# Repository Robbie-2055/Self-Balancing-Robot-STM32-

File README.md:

# STM32 Self-Balancing Robot

A two-wheeled self-balancing inverted pendulum robot built using an **STM32** microcontroller. The robot utilizes an **MPU6050** Inertial Measurement Unit (IMU) to sense its orientation, processes this data through a PID loop, and drives two **DC shaft motors** via an **L298N** motor driver to maintain perfect equilibrium.

This project is split into two distinct execution phases: prototyping with off-the-shelf modules and migrating to a custom-designed Printed Circuit Board (PCB).

---

## 📌 Project Roadmap

- [x] **Phase 1: Breadboard Prototype** 
  - Wire STM32, MPU6050, and L298N on a chassis.
  - Implement basic I2C communication and PWM motor control.
- [ ] **Phase 2: Firmware Optimization**
  - Tune the PID parameters ($K_p$, $K_i$, $K_d$).
- [ ] **Phase 3: Custom PCB Layout**
  - Design a compact, integrated schematic in KiCad

---

## 🛠️ Hardware Architecture

### Phase 1: Prototype Components
* **Microcontroller:** STM32 (e.g., STM32F103C8T6 "Blue Pill") — Handles high-speed sensor parsing, PID calculation, and PWM generation.
* **IMU Sensor:** MPU6050 — Configured via I2C to read accelerometer and gyroscope raw data.
* **Motor Driver:** L298N Dual H-Bridge — Regulates power and direction to the motors based on logic signals from the STM32.
* **Actuators:** 2x DC Gear Shaft Motors (equipped with quadrature encoders for speed feedback).
* **Power Supply:** 3S LiPo battery (11.1V) to power the motors, stepped down via buck converter to 5V/3.3V for logic.

### Phase 2: Custom Board Upgrades
To reduce wiring complexity, eliminate inductive noise, and minimize the physical footprint:
* **Integrated MCU:** STM32 chip placed directly on-board with dedicated decoupling capacitors and an external crystal oscillator.
* **On-board Sensors:** Hardwired MPU6050 footprint to prevent I2C signal degradation over jumper wires.
* **Motor Driver:** The L298N Motor driver together with all support components placed directly on the custom board

---

## Current developments

https://github.com/user-attachments/assets/f44257d5-607a-4bce-967d-3fb6638ffd92

https://github.com/user-attachments/assets/f6ba3c8e-9986-4cd3-9cd2-4a73ed5fd0c9

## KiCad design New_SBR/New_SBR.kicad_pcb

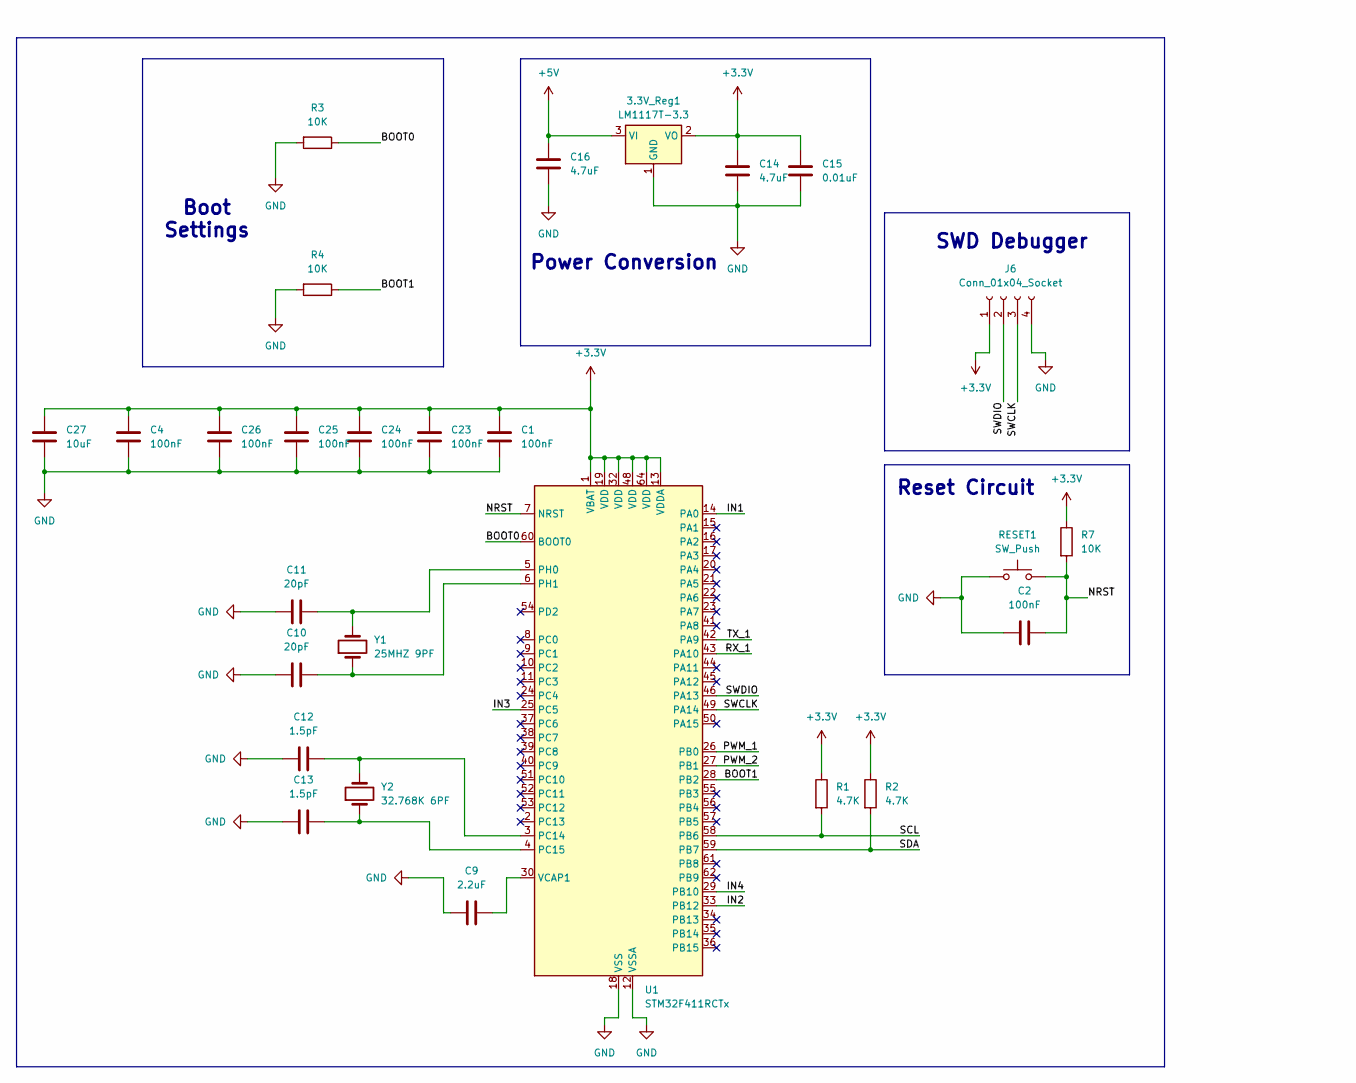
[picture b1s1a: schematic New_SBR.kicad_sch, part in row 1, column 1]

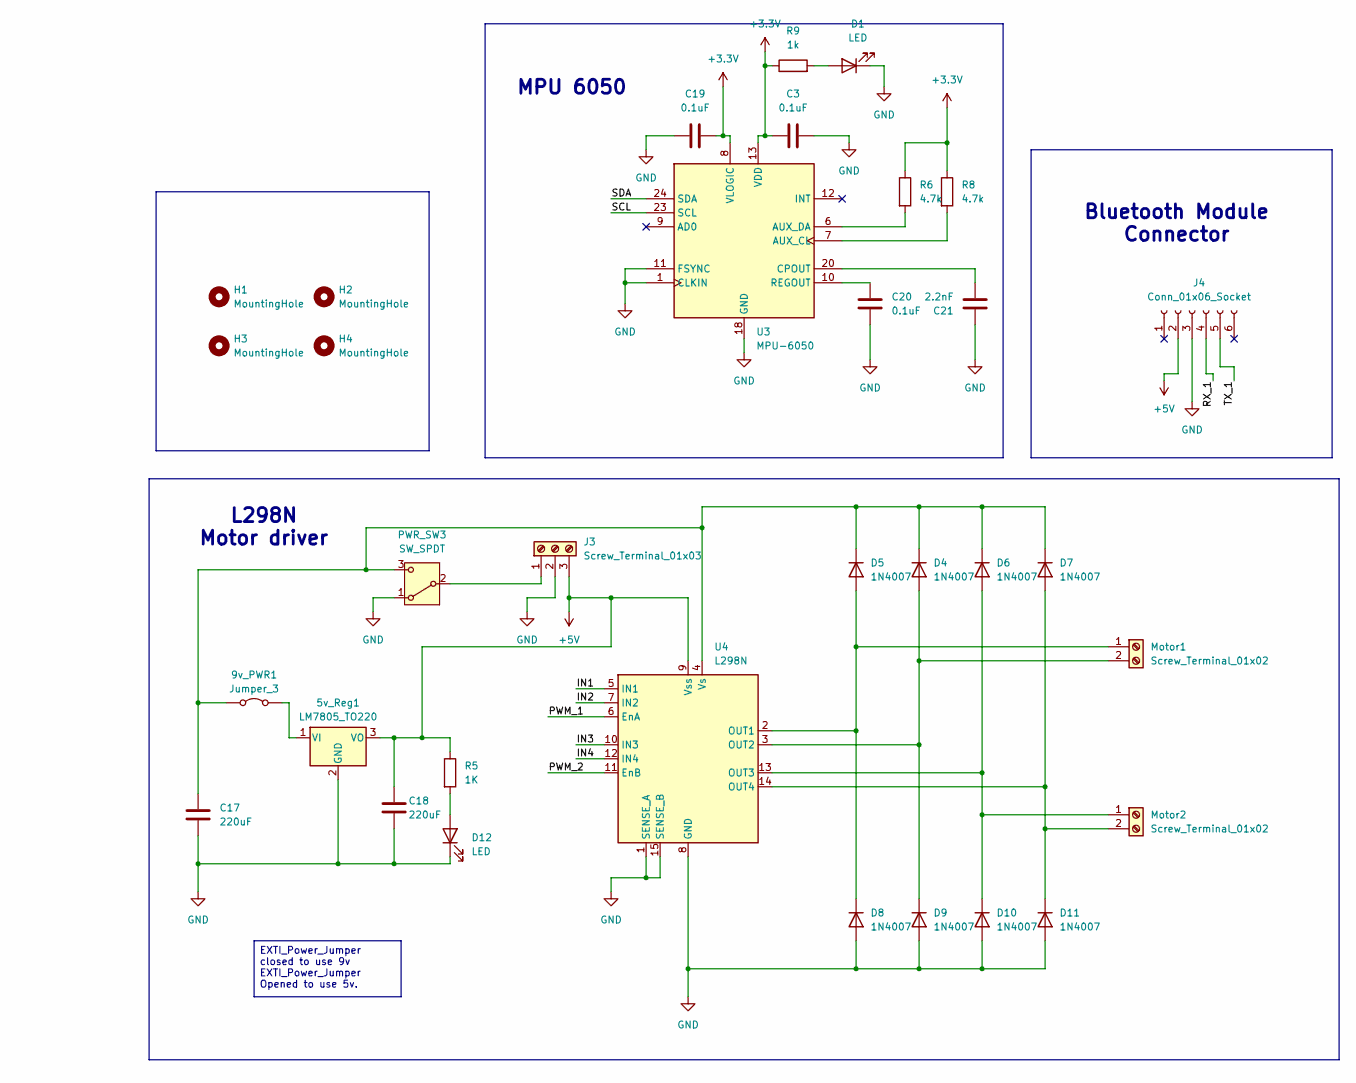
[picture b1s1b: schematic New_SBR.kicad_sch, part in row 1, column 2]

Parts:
3.3V_Reg1: LM1117T-3.3; TO-220-3_Vertical
5v_Reg1: LM7805_TO220; TO-220-3_Vertical
9v_PWR1: Jumper_3; PinHeader_1x02_P2.54mm_Vertical
C1, C2, C4, C23, C24, C25, C26: 100nF; C_0603_1608Metric
C3, C19, C20: 0.1uF; C_0402_1005Metric
C9: 2.2uF; C_0603_1608Metric
C10, C11: 20pF; C_0603_1608Metric
C12, C13: 1.5pF; C_0603_1608Metric
C14, C16: 4.7uF; C_0603_1608Metric
C15: 0.01uF; C_0603_1608Metric
C17, C18: 220uF; C_0603_1608Metric
C21: 2.2nF; C_0402_1005Metric
C27: 10uF; C_0603_1608Metric
D1: LED; LED_0402_1005Metric
D4, D5, D6, D7, D8, D9, D10, D11: 1N4007; D_SMA
D12: LED; LED_0603_1608Metric
H1, H2, H3, H4: MountingHole; MountingHole_2.2mm_M2
J3: Screw_Terminal_01x03; TerminalBlock_Phoenix_MKDS-1,5-3-5.08_1x03_P5.08mm_Horizont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
J4: Conn_01x06_Socket; PinSocket_1x06_P2.54mm_Vertical
J6: Conn_01x04_Socket; PinSocket_1x04_P2.54mm_Vertical
Motor1, Motor2: Screw_Terminal_01x02; TerminalBlock_Phoenix_MKDS-1,5-2-5.08_1x02_P5.08mm_Horizont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
PWR_SW3: SW_SPDT; SW_Slide_SPDT_Straight_CK_OS102011MS2Q
R1, R2: 4.7K; R_0402_1005Metric
R3, R4, R7: 10K; R_0603_1608Metric
R5: 1K; R_0603_1608Metric
R6, R8: 4.7k; R_0402_1005Metric
R9: 1k; R_0402_1005Metric
RESET1: SW_Push; SW_SPST_TL3305A
U1: STM32F411RCTx; LQFP-64_10x10mm_P0.5mm
U3: MPU-6050; InvenSense_QFN-24_4x4mm_P0.5mm_NoMask
U4: L298N; TO-220-15_P2.54x5.08mm_StaggerOdd_Lead4.58mm_Vertical
Y1: 25MHZ 9PF; Crystal_HC49-U_Vertical
Y2: 32.768K 6PF; Crystal_C38-LF_D3.0mm_L8.0mm_Vertical

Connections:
+3.3V: 3.3V_Reg1.2 (VO), C1.2, C3.1, C4.2, C14.2, C15.2, C19.2, C23.2, C24.2, C25.2, C26.2, C27.2, J6.1, R1.1, R2.1, R6.1, R7.1, R8.1, R9.1, U1.1 (VBAT), U1.13 (VDDA), U1.19 (VDD), U1.32 (VDD), U1.48 (VDD), U1.64 (VDD), U3.8 (VLOGIC), U3.13 (VDD)
+5V: 3.3V_Reg1.3 (VI), 5v_Reg1.3 (VO), C16.2, C18.2, J3.3, J4.2, R5.1, U4.9 (Vss)
/BOOT0: R3.1, U1.60 (BOOT0)
/BOOT1: R4.1, U1.28 (PB2)
/IN1: U1.14 (PA0), U4.5 (IN1)
/IN2: U1.33 (PB12), U4.7 (IN2)
/IN3: U1.25 (PC5), U4.10 (IN3)
/IN4: U1.29 (PB10), U4.12 (IN4)
/NRST: C2.1, R7.2, RESET1.2, U1.7 (NRST)
/PWM_1: U1.26 (PB0), U4.6 (EnA)
/PWM_2: U1.27 (PB1), U4.11 (EnB)
/RX_1: J4.4, U1.43 (PA10)
/SCL: R1.2, U1.58 (PB6), U3.23 (SCL)
/SDA: R2.2, U1.59 (PB7), U3.24 (SDA)
/SWCLK: J6.3, U1.49 (PA14)
/SWDIO: J6.2, U1.46 (PA13)
/TX_1: J4.5, U1.42 (PA9)
GND: 3.3V_Reg1.1 (GND), 5v_Reg1.2 (GND), C1.1, C2.2, C3.2, C4.1, C9.1, C10.1, C11.1, C12.1, C13.1, C14.1, C15.1, C16.1, C17.1, C18.1, C19.1, C20.1, C21.2, C23.1, C24.1, C25.1, C26.1, C27.1, D1.1 (K), D8.2 (A), D9.2 (A), D10.2 (A), D11.2 (A), D12.1 (K), J3.2, J4.3, J6.4, PWR_SW3.1 (A), R3.2, R4.2, RESET1.1, U1.12 (VSSA), U1.18 (VSS), U1.31 (VSS), U1.47 (VSS), U1.63 (VSS), U3.1 (CLKIN), U3.11 (FSYNC), U3.18 (GND), U4.1 (SENSE_A), U4.8 (GND), U4.15 (SENSE_B)
unnamed: 5v_Reg1.1 (VI), 9v_PWR1.2 (B)
unnamed: 9v_PWR1.1 (A), C17.2, D4.1 (K), D5.1 (K), D6.1 (K), D7.1 (K), PWR_SW3.3 (C), U4.4 (Vs)
unnamed: D1.2 (A), R9.2
unnamed: D4.2 (A), D9.1 (K), Motor1.2, U4.3 (OUT2)
unnamed: D5.2 (A), D8.1 (K), Motor1.1, U4.2 (OUT1)
unnamed: D6.2 (A), D10.1 (K), Motor2.1, U4.13 (OUT3)
unnamed: D7.2 (A), D11.1 (K), Motor2.2, U4.14 (OUT4)
unnamed: D12.2 (A), R5.2
unnamed: J3.1, PWR_SW3.2 (B)
unnamed: C12.2, U1.3 (PC14), Y2.2
unnamed: C13.2, U1.4 (PC15), Y2.1
unnamed: C11.2, U1.5 (PH0), Y1.2
unnamed: C10.2, U1.6 (PH1), Y1.1
unnamed: C9.2, U1.30 (VCAP1)
unnamed: R8.2, U3.7 (AUX_CL)
unnamed: R6.2, U3.6 (AUX_DA)
unnamed: C21.1, U3.20 (CPOUT)
unnamed: C20.2, U3.10 (REGOUT)

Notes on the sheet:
Boot Settings
L298N Motor driver
Power Conversion
SWD Debugger
Reset Circuit
Bluetooth Module Connector
MPU 6050
EXTI_Power_Jumper closed to use 9v EXTI_Power_Jumper Opened to use 5v.

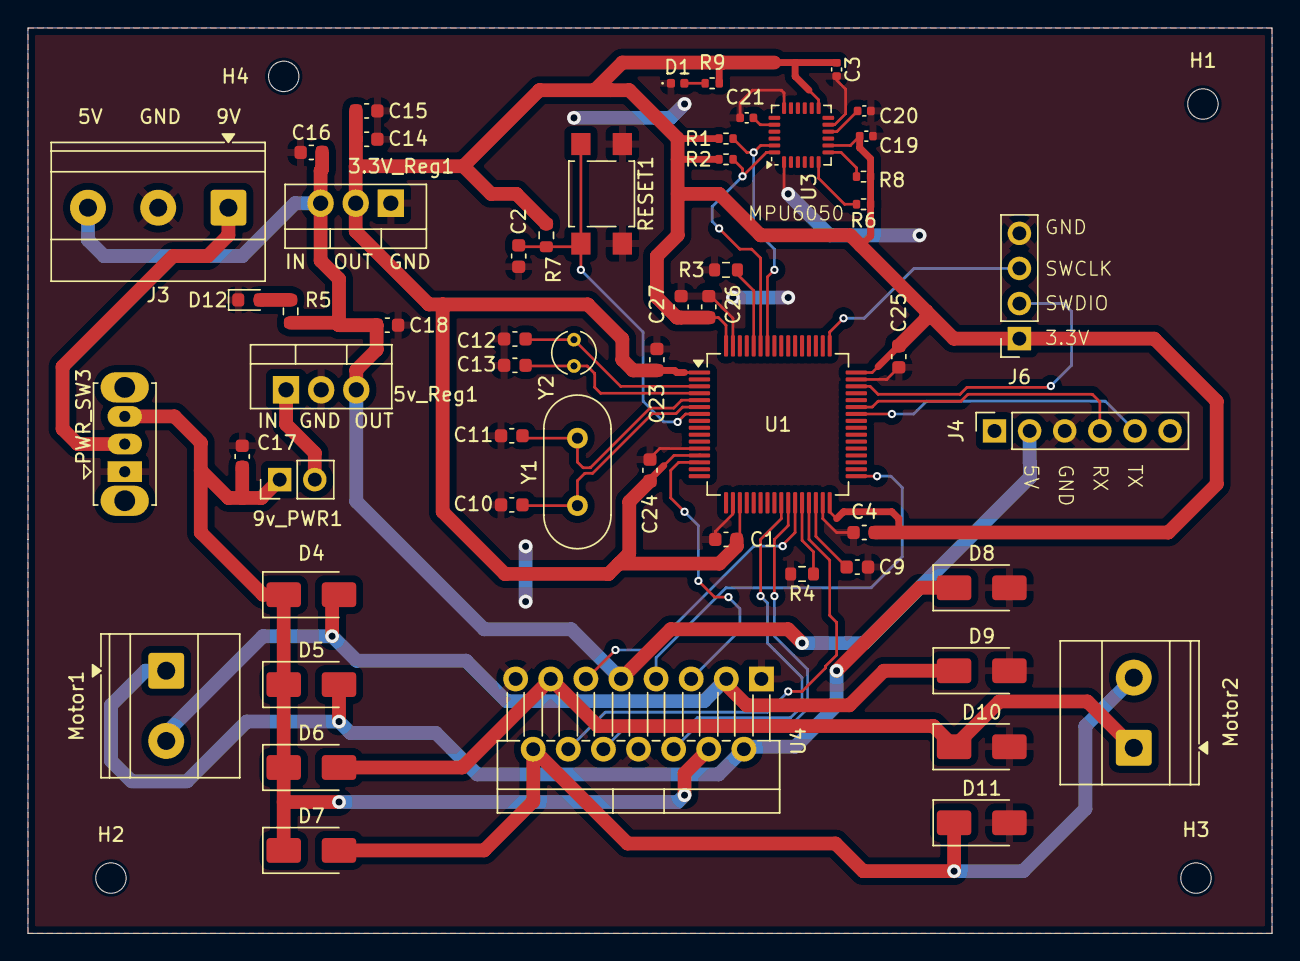
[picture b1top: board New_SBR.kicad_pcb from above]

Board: 2 copper layers, 90.0 x 65.5 mm, 60 parts (0 on the bottom side), 36 nets.

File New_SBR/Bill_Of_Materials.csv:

"Id";"Designator";"Footprint";"Quantity";"Designation";"Supplier and ref";
1;"R2,R1";"R_0402_1005Metric";2;"4.7K";;;
2;"R9";"R_0402_1005Metric";1;"1k";;;
3;"R8,R6";"R_0402_1005Metric";2;"4.7k";;;
4;"D1";"LED_0402_1005Metric";1;"LED";;;
5;"C21";"C_0402_1005Metric";1;"2.2nF";;;
6;"C20,C19,C3";"C_0402_1005Metric";3;"0.1uF";;;
7;"U3";"InvenSense_QFN-24_4x4mm_P0.5mm_NoMask";1;"MPU-6050";;;
8;"U1";"LQFP-64_10x10mm_P0.5mm";1;"STM32F411RCTx";;;
9;"D4,D5,D8,D10,D6,D7,D9,D11";"D_0603_1608Metric";8;"1N4007";;;
10;"C15";"C_0603_1608Metric";1;"0.01uF";;;
11;"C14,C16";"C_0603_1608Metric";2;"4.7uF";;;
12;"C23,C25,C26,C1,C4,C2,C24";"C_0603_1608Metric";7;"100nF";;;
13;"C12,C13";"C_0603_1608Metric";2;"1.5pF";;;
14;"D12";"LED_0603_1608Metric";1;"LED";;;
15;"J1,J2";"TerminalBlock_Xinya_XY308-2.54-2P_1x02_P2.54mm_Horizontal";2;"Screw_Terminal_01x02";;;
16;"U4";"TO-220-15_P2.54x5.08mm_StaggerOdd_Lead4.58mm_Vertical";1;"L298N";;;
17;"R3,R4,R7";"R_0603_1608Metric";3;"10K";;;
18;"J3";"TerminalBlock_Xinya_XY308-2.54-3P_1x03_P2.54mm_Horizontal";1;"Screw_Terminal_01x03";;;
19;"R5";"R_0603_1608Metric";1;"1K";;;
20;"C27";"C_0603_1608Metric";1;"10uF";;;
21;"J4";"PinSocket_1x06_P2.54mm_Vertical";1;"Conn_01x06_Socket";;;
22;"C9";"C_0603_1608Metric";1;"2.2uF";;;
23;"C10,C11";"C_0603_1608Metric";2;"20pF";;;
24;"C17,C18";"C_0603_1608Metric";2;"220uF";;;
25;"PWR_SW3";"SW_Slide_SPDT_Straight_CK_OS102011MS2Q";1;"SW_SPDT";;;
26;"RESET1";"SW_SPST_TL3305A";1;"SW_Push";;;
27;"J6";"PinSocket_1x04_P2.54mm_Vertical";1;"Conn_01x04_Socket";;;
28;"9v_PWR1";"PinHeader_1x02_P2.54mm_Vertical";1;"Jumper_3";;;
29;"5v_Reg1";"TO-220-3_Vertical";1;"LM7805_TO220";;;
30;"3.3V_Reg1";"TO-220-3_Vertical";1;"LM1117T-3.3";;;
31;"Y1";"Crystal_HC49-U_Vertical";1;"25MHZ 9PF";;;
32;"Y2";"Crystal_C38-LF_D3.0mm_L8.0mm_Vertical";1;"32.768K  6PF";;;

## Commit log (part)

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2026-05-19 Rename SelfBalancing_Robot.zip to SelfBalancing_Robot_Code.zip
2026-05-19 Clarify motor description and sensor fusion method
    Updated description to specify 'two DC shaft motors' and replaced 'Complementary Filter' with 'Kalman Filter' in the sensor fusion section.
2026-05-19 Revise sensor fusion and PID control explanations
    Updated sensor fusion and PID control descriptions for clarity.
2026-05-19 Fix formatting of PID control parameters in README
    Updated PID control parameters formatting in README.
2026-05-19 Improve formatting of sensor fusion and control sections
    Reformatted text for better readability in the README.
2026-05-19 Update README with current developments and images
    Removed outdated image links and added current developments section with new images.
